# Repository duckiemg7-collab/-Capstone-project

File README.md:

# firmware_smartcharge

Firmware component copied from ADC/main for SmartCharge project.

Contains example display, wifi/mqtt and power meter code for ESP32 (ESP-IDF).

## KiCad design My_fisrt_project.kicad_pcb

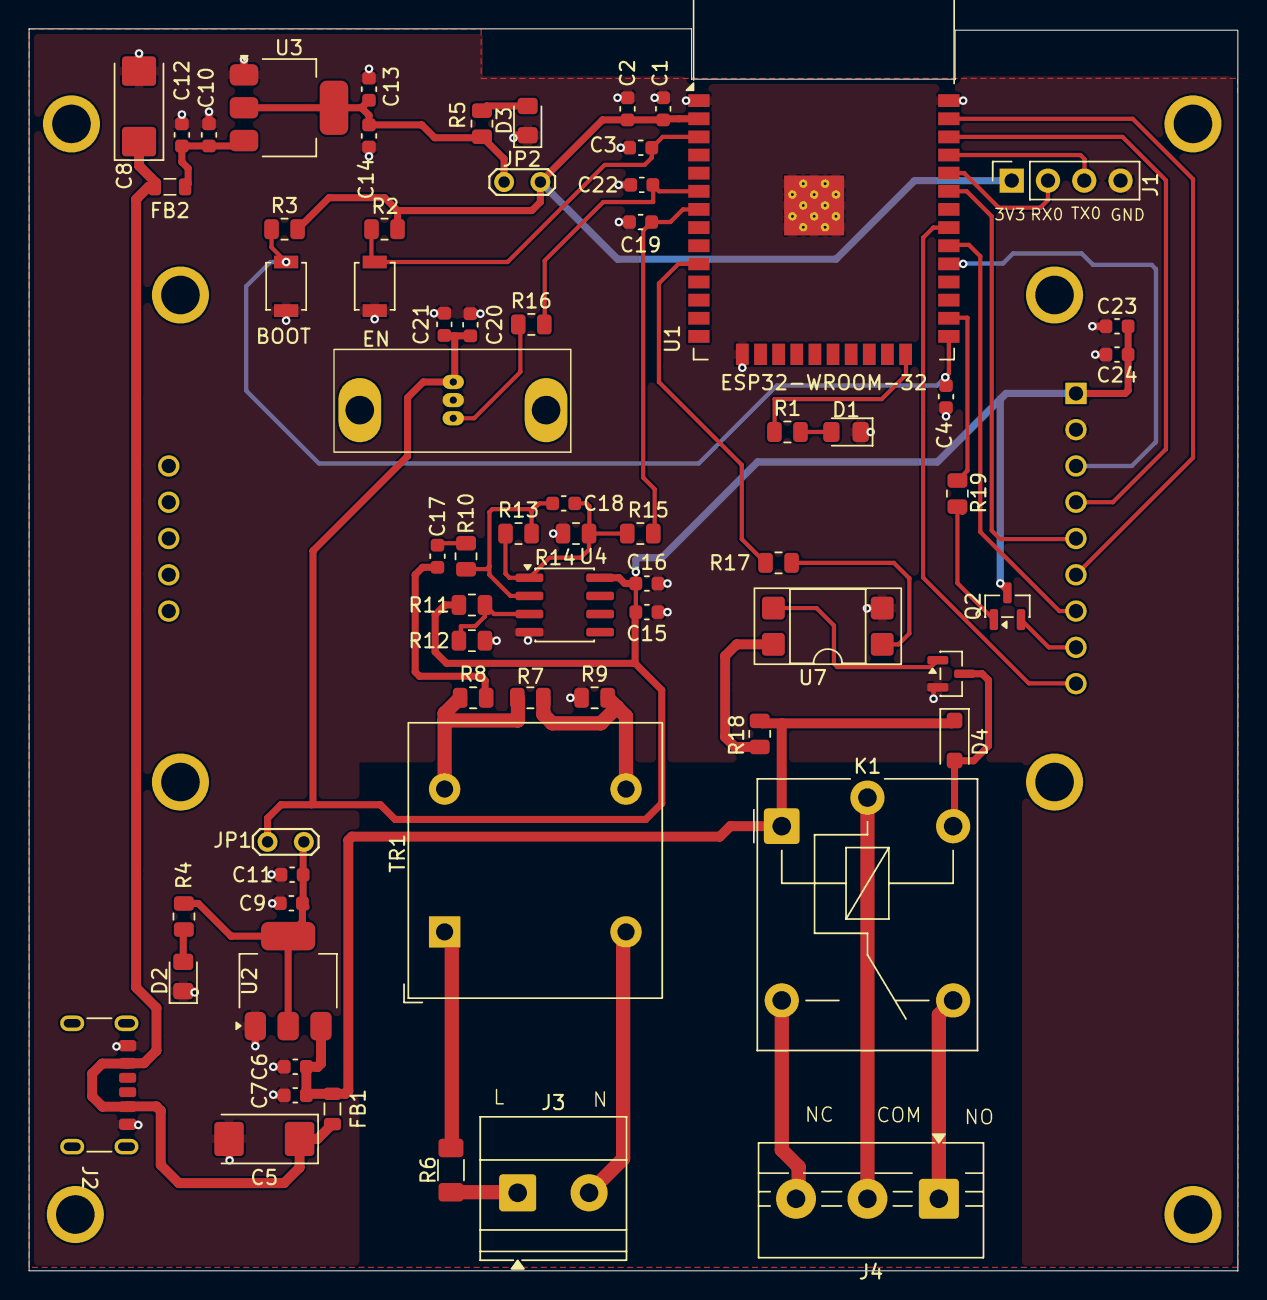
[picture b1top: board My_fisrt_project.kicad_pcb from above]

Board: 2 copper layers, 84.7 x 87.0 mm, 68 parts (1 on the bottom side), 46 nets.

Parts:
BOOT: BOOT; SW_SPST_B3U-1000P
C1, C3, C4, C6, C9, C10, C13, C15, C20, C23: 100nF; C_0603_1608Metric
C2, C7, C11, C12, C14, C16, C21, C24: 10uF; C_0603_1608Metric
C5, C8: C_Polarized_22uF; CP_EIA-6032-28_Kemet-C
C17: 1uF; C_0603_1608Metric
C18: 1nF; C_0603_1608Metric
C19, C22: 22pF; C_0603_1608Metric
D1: LED_Blue; LED_0805_2012Metric_Pad1.15x1.40mm_HandSolder
D2: LED_Red; LED_0805_2012Metric_Pad1.15x1.40mm_HandSolder
D3: LED_Small; LED_0805_2012Metric_Pad1.15x1.40mm_HandSolder
D4: 1N4148W; D_SOD-123F
EN: EN; SW_SPST_B3U-1000P
FB1, FB2: 600Ohm-100Mhz; L_0805_2012Metric
J1: Conn_01x04_Pin; PinSocket_1x04_P2.54mm_Vertical
J2: USB_C_Receptacle_PowerOnly_6P; USB_C_Receptacle_GCT_USB4125-xx-x_6P_TopMnt_Horizontal
J3: Screw_Terminal_01x02; TerminalBlock_Phoenix_MKDS-1,5-2_1x02_P5.00mm_Horizontal
J4: Screw_Terminal_01x03; TerminalBlock_MaiXu_MX126-5.0-03P_1x03_P5.00mm
JP1, JP2: Jumper_2_Bridged; TestPoint_2Pads_Pitch2.54mm_Drill0.8mm
K1: JQC-3FF-005-1Z; Relay_SPDT_Finder_36.11
Q1, Q2: MMBT3904; SOT-23
R1, R2, R3, R4, R5, R10, R11, R12, R14: 10k; R_0805_2012Metric
R6: 200k; R_1206_3216Metric_Pad1.30x1.75mm_HandSolder
R7: 100; R_0805_2012Metric
R8, R9, R15, R16: 0; R_0805_2012Metric
R13: 33k; R_0805_2012Metric
R17: 330; R_0805_2012Metric
R18, R19: 1k; R_0805_2012Metric
TR1: ZMPT101K; Transformer_Zeming_ZMPT101K
U1: ESP32-WROOM-32
U2, U3: AMS1117-3.3; SOT-223-3_TabPin2
U4: LM358; SOIC-8_3.9x4.9mm_P1.27mm
U5: WCS1800
U6: CR2013-MI2120
U7: SFH617A-4X001; DIP-4_W7.62mm_SMDSocket_SmallPads

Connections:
+3.3VA: C15.1, C16.1, C20.1, C21.1, C23.1, C24.1, JP1.2 (B), Q2.3 (C), R11.2, U4.8 (V+), U5.1 (VCC), U6.1 (VCC)
+3V3_ESP: C1.1, C2.1, J1.1, JP2.2 (B), R2.2, R3.2, U1.2 (VDD)
+5V: C6.1, C7.1, D4.1 (K), FB1.1, K1.A1, R18.2, U2.3 (VI)
+5V-IN: C5.1, C8.1, FB1.2, FB2.2, J2.A9 (VBUS), J2.B9 (VBUS)
/IO_RELAY/COM: J4.2, K1.11
/IO_RELAY/NC: J4.1, K1.12
/IO_RELAY/NO: J4.3, K1.14
/ZMPT101B/L: J3.1, R6.2
/ZMPT101B/N: J3.2, TR1.2
/ZMPT101B/VIN_AC: C17.2, R8.2
/mcu/BOOT: BOOT.1 (A), C4.1, R3.1, U1.25 (IO0)
/mcu/EN: C3.1, EN.1 (A), R2.1, U1.3 (EN)
/mcu/OUT2: R1.1, U1.24 (IO2)
/mcu/OUT5: R19.2, U1.26 (IO4)
/mcu/RX0: J1.2, U1.34 (RXD0/IO3)
/mcu/TX0: J1.3, U1.35 (TXD0/IO1)
ADC_WCS1800: C22.1, R16.2, U1.6 (IO34)
ADC_ZMPT101B: C19.1, R15.2, U1.7 (IO35)
CS: U1.29 (IO5), U6.3 (~CS)
DC: U1.33 (IO21), U6.5 (D/~C)
GND: BOOT.2 (B), C1.2, C2.2, C3.2, C4.2, C5.2, C6.2, C7.2, C8.2, C9.2, C10.2, C11.2, C12.2, C13.2, C14.2, C15.2, C16.2, C19.2, C20.2, C21.2, C22.2, C23.2, C24.2, D1.1 (K), D2.1 (K), D3.1 (K), EN.2 (B), J1.4, J2.A12 (GND), J2.B12 (GND), Q1.2 (E), R9.1, R12.1, R14.1, U1.1 (GND), U1.15 (GND), U1.38 (GND), U1.39 (GND), U2.1 (GND), U3.1 (GND), U4.4 (V-), U5.2 (GND), U6.2 (GND), U7.2
LED: Q2.2 (E), U6.8 (LED)
MISO: U1.31 (IO19), U6.9 (MISO)
MOSI: U1.37 (IO23), U6.6 (MOSI)
unnamed: C17.1, R10.2
unnamed: C18.1, R13.1, R14.2, R15.1, U4.1
unnamed: D1.2 (A), R1.2
unnamed: D2.2 (A), R4.2
unnamed: D3.2 (A), R5.2
unnamed: D4.2 (A), K1.A2, Q1.3 (C)
unnamed: C9.1, C11.1, JP1.1 (A), R4.1, U2.2 (VO)
unnamed: C13.1, C14.1, JP2.1 (A), R5.1, U3.2 (VO)
unnamed: Q1.1 (B), U7.3
unnamed: Q2.1 (B), R19.1
unnamed: R6.1, TR1.1
unnamed: R7.1, R9.2, TR1.3
unnamed: R7.2, R8.1, TR1.4
unnamed: R17.1, U7.1
unnamed: R18.1, U7.4
unnamed: C10.1, C12.1, FB2.1, U3.3 (VI)
unnamed: R11.1, R12.2, U4.3 (+)
unnamed: C18.2, R10.1, R13.2, U4.2 (-)
unnamed: R16.1, U5.3 (Vout)
OUT25: R17.2, U1.10 (IO25)
RST: U1.36 (IO22), U6.4 (RESET)
SCK: U1.30 (IO18), U6.7 (SCK)

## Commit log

2026-06-03 Add schematic, PCB, PDF and screenshots
2026-06-03 Add firmware_smartcharge component (copied from ADC/main)
2026-06-03 Reorganize: group firmware into firmware/smartcharge and add hardware/README
2026-06-03 Move hardware files into hardware/
2026-06-03 Initial upload from workspace
